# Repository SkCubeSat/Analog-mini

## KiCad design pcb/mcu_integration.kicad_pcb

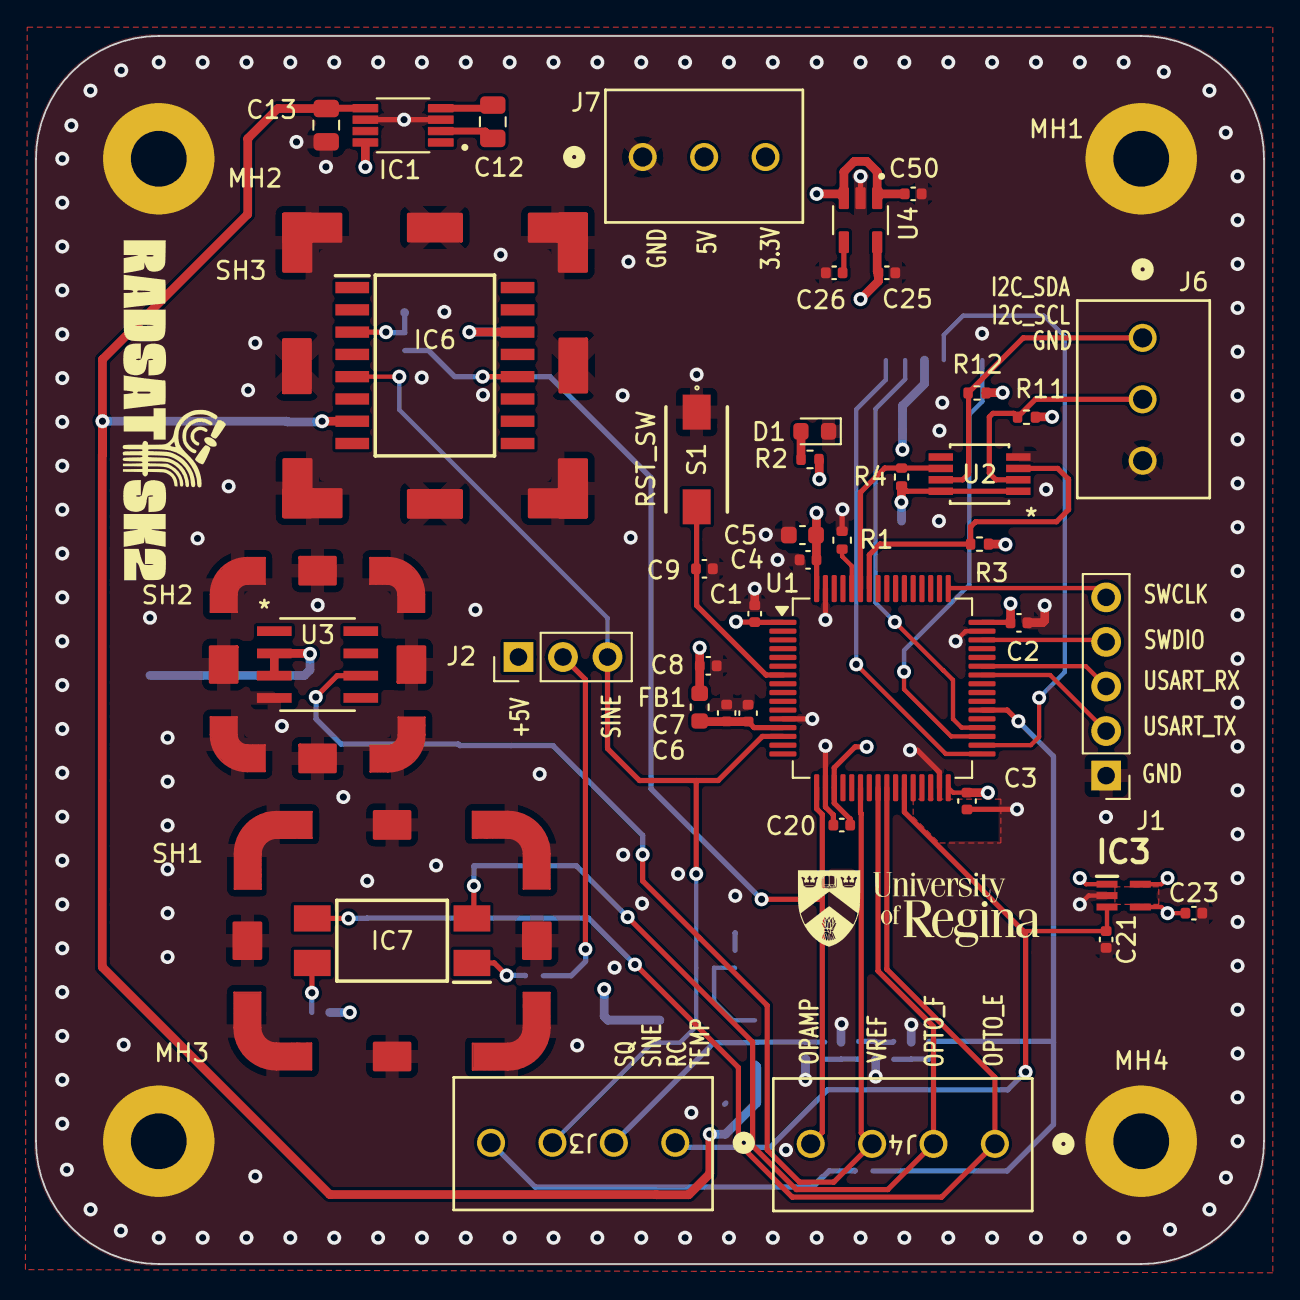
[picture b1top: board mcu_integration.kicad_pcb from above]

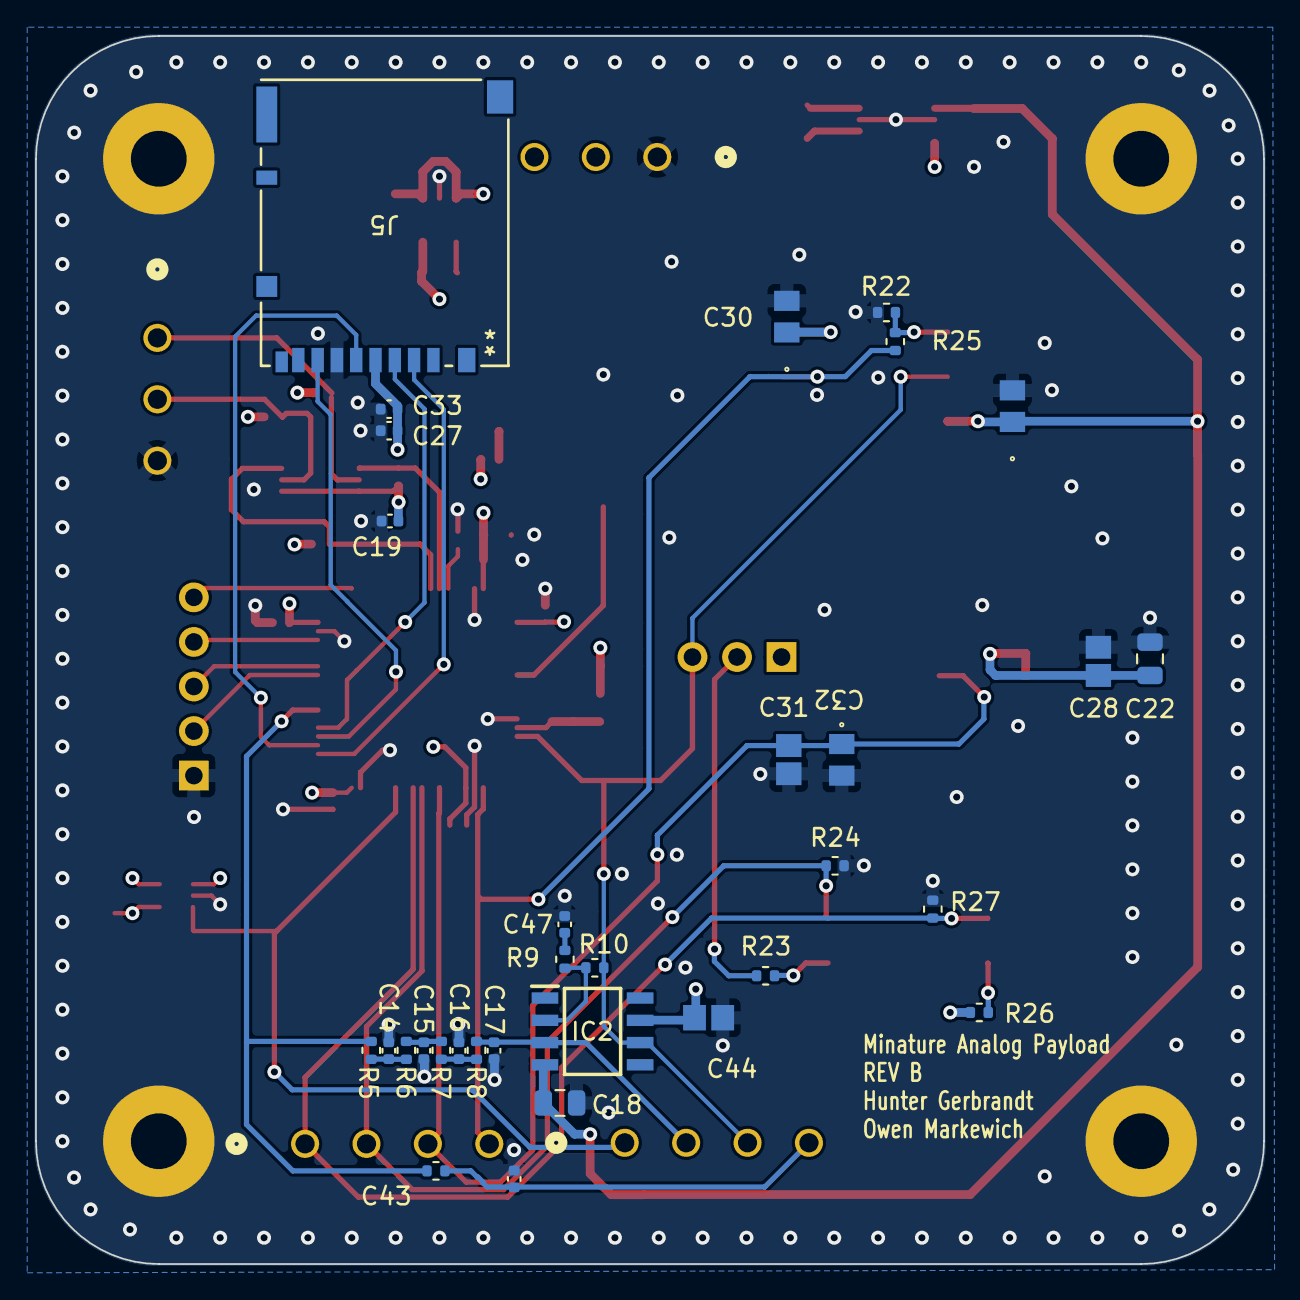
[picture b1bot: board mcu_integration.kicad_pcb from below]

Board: 4 copper layers, 70.0 x 70.0 mm, 79 parts (36 on the bottom side), 41 nets.

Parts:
C1, C2, C3, C4, C6, C9, C20, C27: 100n; C_0402_1005Metric
C5: 10u; C_0603_1608Metric
C7, C8, C33: 1u; C_0402_1005Metric
C12, C13, C22: 10u; C_0805_2012Metric
C14, C15, C16, C17: 0.47u; C_0402_1005Metric
C18: 0.1u; C_0805_2012Metric
C19: 10n; C_0402_1005Metric
C21: 0.22n; C_0402_1005Metric
C23, C26, C43: 0.01u; C_0402_1005Metric
C25: 2.2u; C_0402_1005Metric
C28, C32, C44: 0.1u; CAPC220145_88N_KEM-0.1u
C29, C30: 0.22u; C0805-0.22u
C31: 1u; C0805-1u
C47: 4.7u; C_0402_1005Metric
C50: 0.1u; C_0402_1005Metric
D1: RED; LED_0603_1608Metric
FB1: FerriteBead; L_0603_1608Metric
IC1: TL7660IDGKR; SOP65P490X110-8N-actual
IC2: TL081IDT; SOIC127P600X175-8N
IC3: LMT87DCKT; SOT65P210X110-5N
IC6: AD844_OPAMP_AL; SOIC127P1032X265-16N-AD844
IC7: FOD814_OPTO_AL; SOP254P1016X385-4N-FOD
J1: Conn_01x05; PinHeader_1x05_P2.54mm_Vertical
J2: Conn_01x03; PinHeader_1x03_P2.54mm_Vertical
J3, J4: 1751264; CONN_1751264_PXC
J5: DM3BT-DSF-PEJS; DM3BT_DSF_PEJS
J6, J7: 1751251; CONN_1751251_PXC
MH1, MH2, MH3, MH4: MountingHole_Pad; MountingHole_3.18mm_6.35mm_Pad
R1, R2: 2.2k; R_0402_1005Metric
R3, R4, R10, R11, R12: 10K; R_0402_1005Metric
R5, R6, R7, R8: 3.3K; R_0402_1005Metric
R9: 1K; R_0402_1005Metric
R22: 100k; R_0402_1005Metric
R23: 820; R_0402_1005Metric
R24: 47; R_0402_1005Metric
R25: 1k; R_0402_1005Metric
R26, R27: 100; R_0402_1005Metric
R32: 56k; R_0402_1005Metric
S1: RST_SW; 95C04A3GWRT
SH1: FOD814_SHIELD; FOD814 Shield
SH2: REF192_SHIELD; REF192 Shield
SH3: AD844_SHIELD; AD844 Shield
U1: STM32F103RBTx; LQFP-64_10x10mm_P0.5mm
U2: LTC4300A-1IMS8_PBF
U3: REF192_AL; R_8_ADI-REF
U4: TPS79933QDDCRQ1; SOT95P280X110-5N

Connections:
3.3V Output: C1.1, C2.1, C3.1, C4.1, C5.1, C8.1, C19.2, C20.1, C25.1, C27.1, C33.1, FB1.2, J5.4 (VDD), J7.3, R2.1, R3.1, R4.1, R11.1, R12.1, U1.1 (VBAT), U1.19 (VDD), U1.32 (VDD), U1.48 (VDD), U1.64 (VDD), U2.1 (ENABLE), U2.8 (VCC), U4.5 (OUT)
+5V: C22.1 (+), C23.1, C28.1, C30.1, C44.1, C50.1, IC1.8 (VCC), IC2.7 (VCC+), IC3.1 (VDD_1), IC3.4 (VDD_2), IC3.5 (VDD_3), IC6.14 (V+), J2.1, J7.2, R26.2, U3.2 (VS), U3.3 (*SLEEP), U4.1 (IN), U4.3 (EN)
-5V Output: C13.2 (-), C18.1, C29.1, IC1.5 (VOUT), IC2.4 (VCC-), IC6.7 (V-)
/BOOT0: R1.1, U1.60 (BOOT0)
/NRST: C9.2, S1.2, U1.7 (NRST)
/SPI2_CS_NSS: J5.2 (CD/DAT3), U1.33 (PB12)
/SPI2_MISO: J5.7 (DAT0), U1.35 (PB14)
/SPI2_MOSI: J5.3 (CMD), U1.36 (PB15)
/SPI2_SCK: J5.5 (CLK), U1.34 (PB13)
/SWCLK: J1.4, U1.49 (PA14)
/SWDIO: J1.3, U1.46 (PA13)
/USART1_RX: J1.2, U1.43 (PA10)
/USART1_TX: J1.1, U1.42 (PA9)
ADC1_IN0_SINE: IC2.6 (OUTPUT), IC6.5 (+IN), J2.3, J3.3, R10.1, U1.14 (PA0)
ADC1_IN3_OPAMP_AL: IC6.12 (OUTPUT), J4.4, R25.1, U1.17 (PA3)
ADC1_IN6_VREF_AL: C31.1, C32.1, J4.3, U1.22 (PA6), U3.6 (OUTPUT)
ADC1_IN9_LMT87: C21.1, IC3.3 (OUT), J3.1, U1.27 (PB1)
ADC1_IN14_OPTO_F_AL: IC7.2 (KA), J4.2, R24.1, U1.24 (PC4)
ADC1_IN15_OPTO_E_AL: IC7.3 (E), J4.1, R27.2, U1.25 (PC5)
GND: C1.2, C2.2, C3.2, C4.2, C5.2, C6.2, C7.2, C8.2, C9.1, C13.1 (+), C14.2, C15.2, C16.2, C17.2, C18.2, C19.1, C20.2, C21.2, C22.2 (-), C23.2, C25.2, C26.2, C27.2, C28.2, C29.2, C30.2, C31.2, C32.2, C33.2, C43.1, C44.2, C47.2, C50.2, D1.1 (K), IC1.3 (GND), IC1.6 (LV), IC3.2 (GND), J1.5, J5.6 (VSS), J6.3, J7.1, MH1.1 (1_1), MH2.1 (1_1), MH3.1 (1_1), MH4.1 (1_1), R1.2, R22.1, R24.2, R27.1, S1.1, SH1.1 (GND_1), SH2.1 (GND_1), SH3.1 (GND_1), U1.12 (VSSA), U1.18 (VSS), U1.31 (VSS), U1.47 (VSS), U1.63 (VSS), U2.4 (GND), U3.4 (GND), U4.2 (GND)
I2C_SCL: J6.2, R11.2, U2.2 (SCLOUT)
I2C_SDA: J6.1, R12.2, U2.7 (SDAOUT)
unnamed: C12.1 (+), IC1.2 (CAP+)
unnamed: C12.2 (-), IC1.4 (CAP-)
unnamed: C14.1, R5.2, R6.1
unnamed: C15.1, R6.2, R7.1
unnamed: C16.1, R7.2, R8.1
unnamed: C43.2, J3.4, R32.2
unnamed: C47.1, R9.2
unnamed: D1.2 (A), R2.2
unnamed: IC2.2 (INVERTING_INPUT), R9.1, R10.2
unnamed: IC6.3 (-IN), R22.2, R25.2
unnamed: IC7.1 (AK), R23.1
unnamed: IC7.4 (C), R26.1
unnamed: J2.2, R23.2
unnamed: C6.1, C7.1, FB1.1, U1.13 (VDDA)
unnamed: C26.1, U4.4 (NR)
OBC_I2C_SCL: R3.2, U1.58 (PB6), U2.3 (SCLIN)
OBC_I2C_SDA: R4.2, U1.59 (PB7), U2.6 (SDAIN)
RC_OUTPUT: C17.1, IC2.3 (NON-INVERTING_INPUT), J3.2, R8.2
SIG_SQUARE: R5.1, R32.1, U1.38 (PC7)
